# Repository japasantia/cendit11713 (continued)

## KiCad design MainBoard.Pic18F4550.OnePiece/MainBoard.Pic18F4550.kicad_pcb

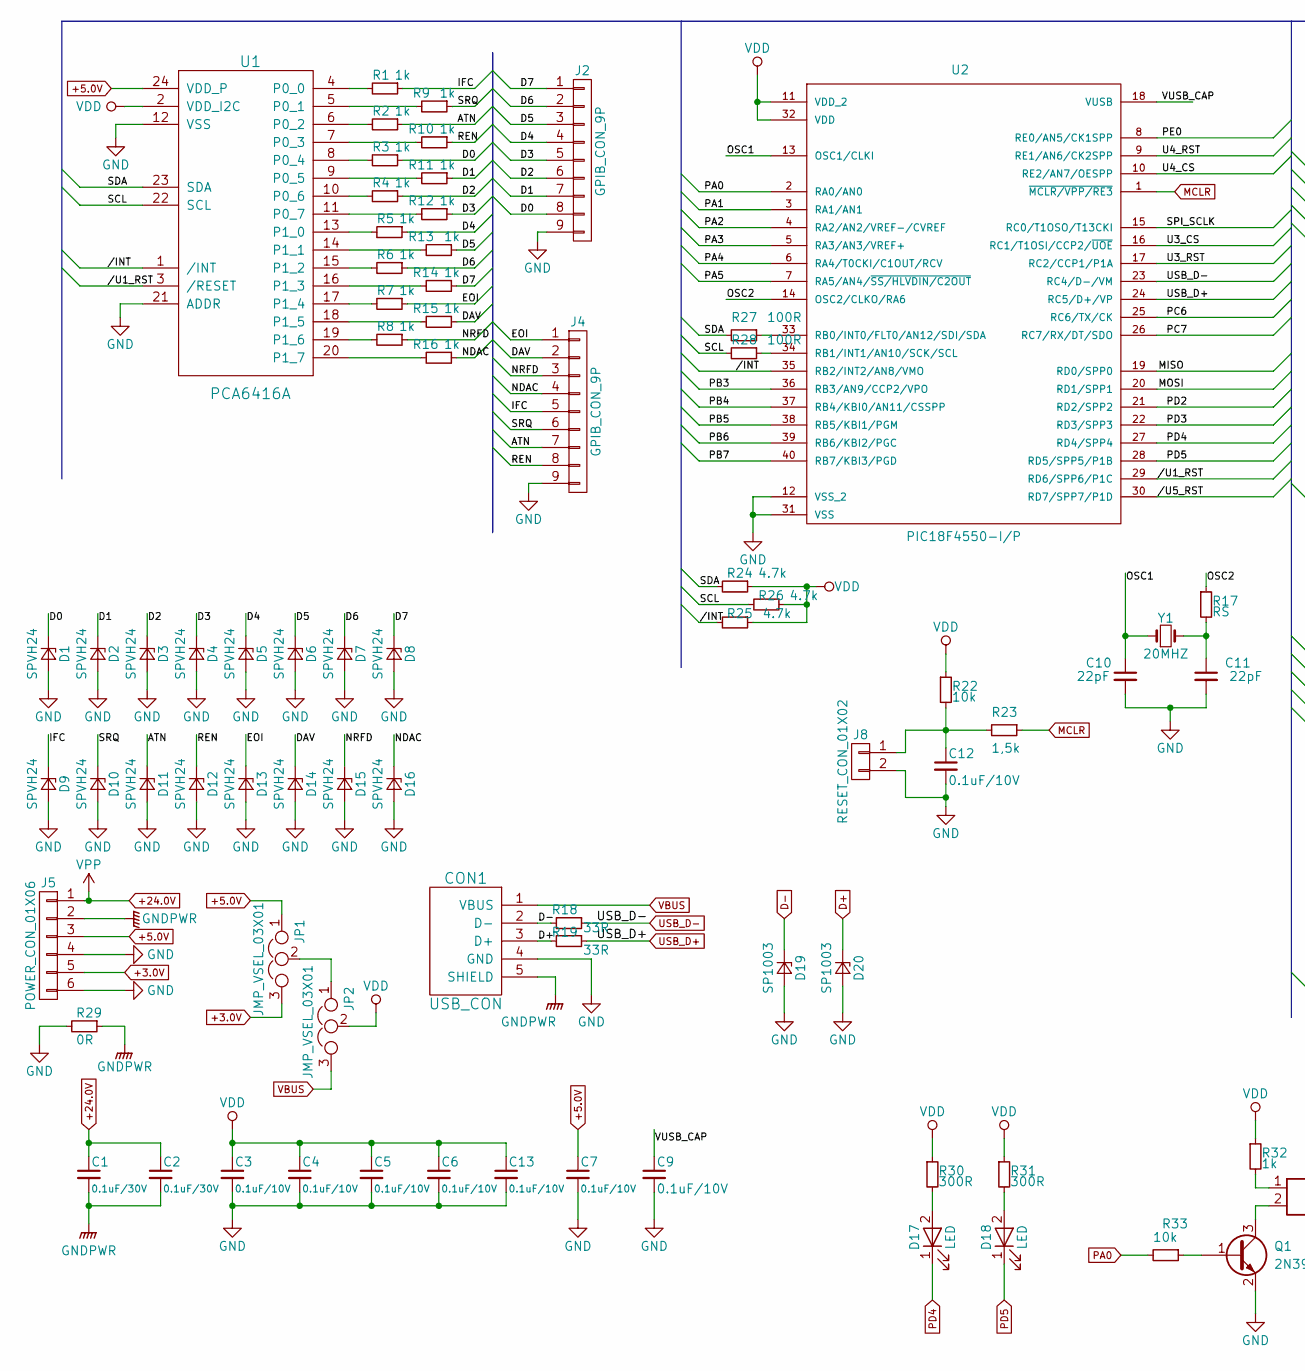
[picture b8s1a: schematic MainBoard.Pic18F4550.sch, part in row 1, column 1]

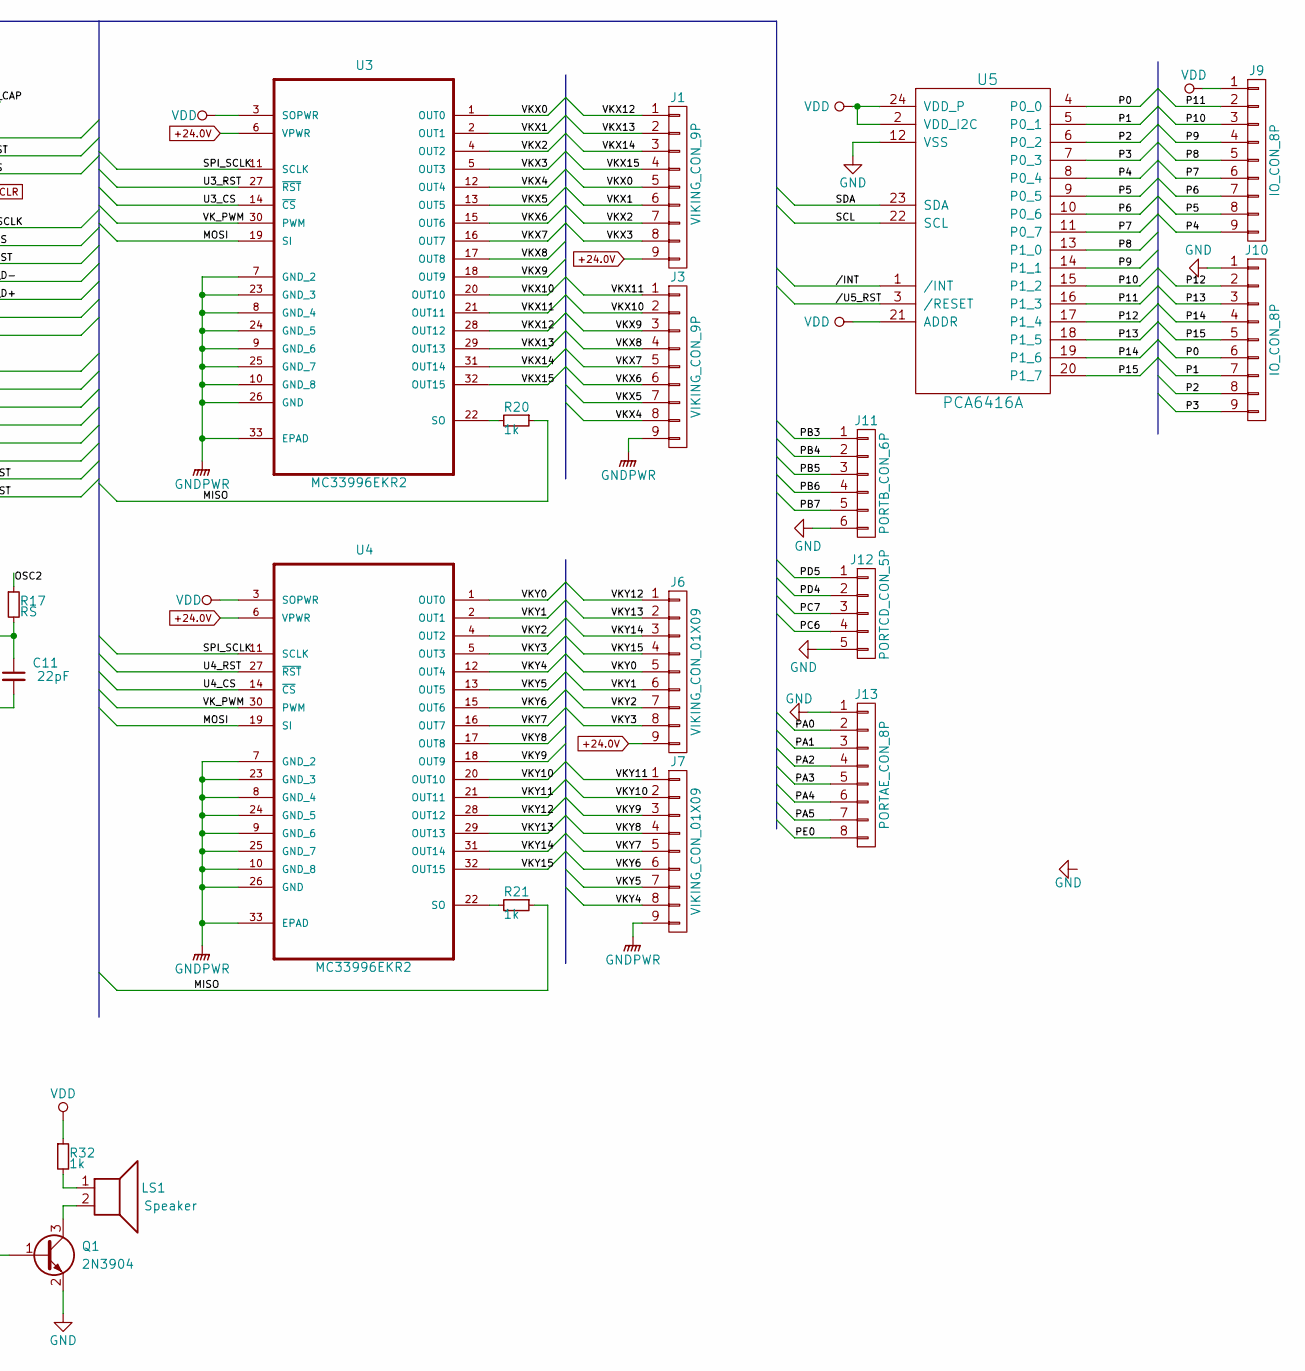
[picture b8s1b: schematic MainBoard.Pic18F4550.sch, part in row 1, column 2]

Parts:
C1, C2: 0.1uF/30V; C_1206_HandSoldering
C3, C4, C5, C6, C7, C13: 0.1uF/10V; C_1206_HandSoldering
C9, C12: 0.1uF/10V; C_0805_HandSoldering
C10, C11: 22pF; C_0805_HandSoldering
CON1: USB_CON; USB_SMT_B
D1, D2, D3, D4, D5, D6, D7, D8, D9, D10, D11, D12, D13, D14, D15, D16: SPVH24; SPHV24-SOD882
D17, D18: LED; LED_0805_HandSoldering
D19, D20: SP1003; SP1003-01ETG
J1, J3: VIKING_CON_9P; Pin_Header_Straight_1x09_Pitch2.54mm
J2, J4: GPIB_CON_9P; Pin_Header_Straight_1x09_Pitch2.54mm
J5: POWER_CON_01X06; Pin_Header_Straight_1x06_Pitch2.54mm
J6, J7: VIKING_CON_01X09; Pin_Header_Straight_1x09_Pitch2.54mm
J8: RESET_CON_01X02; Pin_Header_Straight_1x02_Pitch2.54mm
J9, J10: IO_CON_8P; Pin_Header_Straight_1x09_Pitch2.54mm
J11: PORTB_CON_6P; Pin_Header_Straight_1x06_Pitch2.54mm
J12: PORTCD_CON_5P; Pin_Header_Straight_1x05_Pitch2.54mm
J13: PORTAE_CON_8P; Pin_Header_Straight_1x08_Pitch2.54mm
JP1, JP2: JMP_VSEL_03X01; Pin_Header_Straight_1x03_Pitch2.54mm
LS1: Speaker; MagneticBuzzer_Kingstate_KCG0601
Q1: 2N3904; SOT-23
R1, R2, R3, R4, R5, R6, R7, R8, R9, R10, R11, R12, R13, R14, R15, R16, R20, R21, R32: 1k; R_0805_HandSoldering
R17: RS; R_0805_HandSoldering
R18, R19: 33R; R_0805_HandSoldering
R22, R33: 10k; R_0805_HandSoldering
R23: 1,5k; R_0805_HandSoldering
R24, R25, R26: 4.7k; R_0805_HandSoldering
R27, R28: 100R; R_0805_HandSoldering
R29: 0R; R_0805_HandSoldering
R30, R31: 300R; R_0805_HandSoldering
U1, U5: PCA6416A; PCA6416A-TSSOP24
U2: PIC18F4550-I/P; PIC18F4550-PDIP
U3, U4: MC33996EKR2; MC33996-SOIC32
Y1: 20MHZ; Crystal_SMD_HC49-SD

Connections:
+3.0V: J5.5, JP1.3
+5.0V: C7.1, J5.3, JP1.1, U1.24 (VDD_P)
+24.0V: C1.1, C2.1, J1.9, J5.1, J6.9, U3.6 (VPWR), U4.6 (VPWR)
//INT: R25.2, U1.1 (/INT), U2.35 (RB2/INT2/AN8/VMO), U5.1 (/INT)
//U1_RST: U1.3 (/RESET), U2.29 (RD6/SPP6/P1C)
//U5_RST: U2.30 (RD7/SPP7/P1D), U5.3 (/RESET)
/ATN: D11.1 (K), J4.7, R2.1
/D0: D1.1 (K), J2.8, R3.1
/D1: D2.1 (K), J2.7, R11.1
/D2: D3.1 (K), J2.6, R4.1
/D3: D4.1 (K), J2.5, R12.1
/D4: D5.1 (K), J2.4, R5.1
/D5: D6.1 (K), J2.3, R13.1
/D6: D7.1 (K), J2.2, R6.1
/D7: D8.1 (K), J2.1, R14.1
/DAV: D14.1 (K), J4.2, R15.1
/EOI: D13.1 (K), J4.1, R7.1
/IFC: D9.1 (K), J4.5, R1.1
/MISO: R20.1, R21.1, U2.19 (RD0/SPP0)
/MOSI: U2.20 (RD1/SPP1), U3.19 (SI), U4.19 (SI)
/NDAC: D16.1 (K), J4.4, R16.1
/NRFD: D15.1 (K), J4.3, R8.1
/OSC1: C10.1, U2.13 (OSC1/CLKI), Y1.1
/OSC2: R17.1, U2.14 (OSC2/CLKO/RA6)
/P0: J10.6, U5.4 (P0_0)
/P1: J10.7, U5.5 (P0_1)
/P2: J10.8, U5.6 (P0_2)
/P3: J10.9, U5.7 (P0_3)
/P4: J9.9, U5.8 (P0_4)
/P5: J9.8, U5.9 (P0_5)
/P6: J9.7, U5.10 (P0_6)
/P7: J9.6, U5.11 (P0_7)
/P8: J9.5, U5.13 (P1_0)
/P9: J9.4, U5.14 (P1_1)
/P10: J9.3, U5.15 (P1_2)
/P11: J9.2, U5.16 (P1_3)
/P12: J10.2, U5.17 (P1_4)
/P13: J10.3, U5.18 (P1_5)
/P14: J10.4, U5.19 (P1_6)
/P15: J10.5, U5.20 (P1_7)
/PA1: J13.3, U2.3 (RA1/AN1)
/PA2: J13.4, U2.4 (RA2/AN2/VREF-/CVREF)
/PA3: J13.5, U2.5 (RA3/AN3/VREF+)
/PA4: J13.6, U2.6 (RA4/T0CKI/C1OUT/RCV)
/PA5: J13.7, U2.7 (RA5/AN4/~SS/HLVDIN/C2OUT)
/PB3: J11.1, U2.36 (RB3/AN9/CCP2/VPO)
/PB4: J11.2, U2.37 (RB4/KBI0/AN11/CSSPP)
/PB5: J11.3, U2.38 (RB5/KBI1/PGM)
/PB6: J11.4, U2.39 (RB6/KBI2/PGC)
/PB7: J11.5, U2.40 (RB7/KBI3/PGD)
/PC6: J12.4, U2.25 (RC6/TX/CK)
/PC7: J12.3, U2.26 (RC7/RX/DT/SDO)
/PE0: J13.8, U2.8 (RE0/AN5/CK1SPP)
/REN: D12.1 (K), J4.8, R10.1
/SCL: R26.2, R28.2, U1.22 (SCL), U5.22 (SCL)
/SDA: R24.2, R27.2, U1.23 (SDA), U5.23 (SDA)
/SPI_SCLK: U2.15 (RC0/T1OSO/T13CKI), U3.11 (SCLK), U4.11 (SCLK)
/SRQ: D10.1 (K), J4.6, R9.1
/U3_CS: U2.16 (RC1/T1OSI/CCP2/~UOE), U3.14 (~CS)
/U3_RST: U2.17 (RC2/CCP1/P1A), U3.27 (~RST)
/U4_CS: U2.10 (RE2/AN7/OESPP), U4.14 (~CS)
/U4_RST: U2.9 (RE1/AN6/CK2SPP), U4.27 (~RST)
/VKX0: J1.5, U3.1 (OUT0)
/VKX1: J1.6, U3.2 (OUT1)
/VKX2: J1.7, U3.4 (OUT2)
/VKX3: J1.8, U3.5 (OUT3)
/VKX4: J3.8, U3.12 (OUT4)
/VKX5: J3.7, U3.13 (OUT5)
/VKX6: J3.6, U3.15 (OUT6)
/VKX7: J3.5, U3.16 (OUT7)
/VKX8: J3.4, U3.17 (OUT8)
/VKX9: J3.3, U3.18 (OUT9)
/VKX10: J3.2, U3.20 (OUT10)
/VKX11: J3.1, U3.21 (OUT11)
/VKX12: J1.1, U3.28 (OUT12)
/VKX13: J1.2, U3.29 (OUT13)
/VKX14: J1.3, U3.31 (OUT14)
/VKX15: J1.4, U3.32 (OUT15)
/VKY0: J6.5, U4.1 (OUT0)
/VKY1: J6.6, U4.2 (OUT1)
/VKY2: J6.7, U4.4 (OUT2)
/VKY3: J6.8, U4.5 (OUT3)
/VKY4: J7.8, U4.12 (OUT4)
/VKY5: J7.7, U4.13 (OUT5)
/VKY6: J7.6, U4.15 (OUT6)
/VKY7: J7.5, U4.16 (OUT7)
/VKY8: J7.4, U4.17 (OUT8)
/VKY9: J7.3, U4.18 (OUT9)
/VKY10: J7.2, U4.20 (OUT10)
/VKY11: J7.1, U4.21 (OUT11)
/VKY12: J6.1, U4.28 (OUT12)
/VKY13: J6.2, U4.29 (OUT13)
/VKY14: J6.3, U4.31 (OUT14)
/VKY15: J6.4, U4.32 (OUT15)
/VK_PWM: U3.30 (PWM), U4.30 (PWM)
/VUSB_CAP: C9.1, U2.18 (VUSB)
D+: CON1.3 (D+), D20.1 (K), R19.2
D-: CON1.2 (D-), D19.1 (K), R18.2
GND: C3.2, C4.2, C5.2, C6.2, C7.2, C9.2, C10.2, C11.2, C12.2, C13.2, CON1.4 (GND), D1.2 (A), D2.2 (A), D3.2 (A), D4.2 (A), D5.2 (A), D6.2 (A), D7.2 (A), D8.2 (A), D9.2 (A), D10.2 (A), D11.2 (A), D12.2 (A), D13.2 (A), D14.2 (A), D15.2 (A), D16.2 (A), D19.2 (A), D20.2 (A), J2.9, J4.9, J5.4, J5.6, J8.2, J10.1, J11.6, J12.5, J13.1, Q1.2 (E), R29.2, U1.12 (VSS), U1.21 (ADDR), U2.12 (VSS_2), U2.31 (VSS), U5.12 (VSS)
GNDPWR: C1.2, C2.2, CON1.5 (SHIELD), J3.9, J5.2, J7.9, R29.1, U3.7 (GND_2), U3.8 (GND_4), U3.9 (GND_6), U3.10 (GND_8), U3.23 (GND_3), U3.24 (GND_5), U3.25 (GND_7), U3.26 (GND), U3.33 (EPAD), U4.7 (GND_2), U4.8 (GND_4), U4.9 (GND_6), U4.10 (GND_8), U4.23 (GND_3), U4.24 (GND_5), U4.25 (GND_7), U4.26 (GND), U4.33 (EPAD)
MCLR: R23.1, U2.1 (~MCLR/VPP/RE3)
unnamed: C11.1, R17.2, Y1.2
unnamed: C12.1, J8.1, R22.2, R23.2
unnamed: D17.2 (A), R30.2
unnamed: D18.2 (A), R31.2
unnamed: JP1.2, JP2.1
unnamed: LS1.1, R32.2
unnamed: LS1.2, Q1.3 (C)
unnamed: Q1.1 (B), R33.1
unnamed: R1.2, U1.4 (P0_0)
unnamed: R2.2, U1.6 (P0_2)
unnamed: R3.2, U1.8 (P0_4)
unnamed: R4.2, U1.10 (P0_6)
unnamed: R5.2, U1.13 (P1_0)
unnamed: R6.2, U1.15 (P1_2)
unnamed: R7.2, U1.17 (P1_4)
unnamed: R8.2, U1.19 (P1_6)
unnamed: R9.2, U1.5 (P0_1)
unnamed: R10.2, U1.7 (P0_3)
unnamed: R11.2, U1.9 (P0_5)
unnamed: R12.2, U1.11 (P0_7)
unnamed: R13.2, U1.14 (P1_1)
unnamed: R14.2, U1.16 (P1_3)
unnamed: R15.2, U1.18 (P1_5)
unnamed: R16.2, U1.20 (P1_7)
unnamed: R20.2, U3.22 (SO)
unnamed: R21.2, U4.22 (SO)
unnamed: R27.1, U2.33 (RB0/INT0/FLT0/AN12/SDI/SDA)
unnamed: R28.1, U2.34 (RB1/INT1/AN10/SCK/SCL)
PA0: J13.2, R33.2, U2.2 (RA0/AN0)
PD4: D17.1 (K), J12.2, U2.27 (RD4/SPP4)
PD5: D18.1 (K), J12.1, U2.28 (RD5/SPP5/P1B)
USB_D+: R19.1, U2.24 (RC5/D+/VP)
USB_D-: R18.1, U2.23 (RC4/D-/VM)
VBUS: CON1.1 (VBUS), JP2.3
VDD: C3.1, C4.1, C5.1, C6.1, C13.1, J9.1, JP2.2, R22.1, R24.1, R25.1, R26.1, R30.1, R31.1, R32.1, U1.2 (VDD_I2C), U2.11 (VDD_2), U2.32 (VDD), U3.3 (SOPWR), U4.3 (SOPWR), U5.2 (VDD_I2C), U5.21 (ADDR), U5.24 (VDD_P)

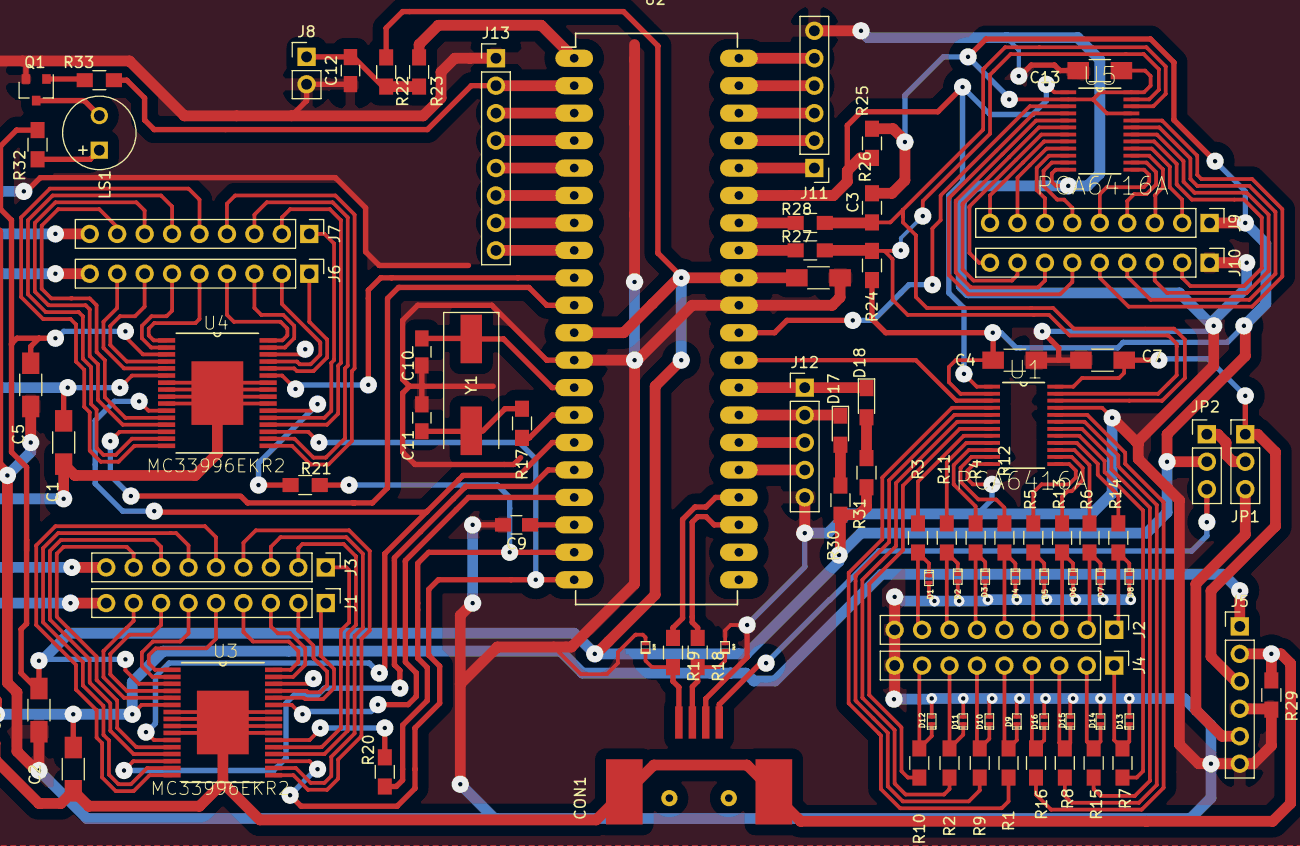
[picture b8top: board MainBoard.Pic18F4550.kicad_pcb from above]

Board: 2 copper layers, 89 parts (0 on the bottom side), 136 nets.

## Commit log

2018-01-09 Commit para restaurar repo
    - Respaldo ante problemas en pull
2018-01-13 Revision de PCBs + MergedPcbs
    - Se revisan PCBs
    - VikingPortExpander
    - GpibPortExpander
    - MainBoards en tres versiones
    - Se genera archivos Gerber que combina estos PCBs en un documento
2018-01-15 Revision de MainBoard.OnePiece
2018-01-16 Revision de merged PCBs
    - Ultima revision para fabricacion PCBs
    - No se hacen cambios en este con respecto al commit anterior
2018-01-18 Respaldo de archivos modificados
    - Aparecend modificados, pero no se ha trabajado en ellos
2018-01-29 Se comienza diseño de interfaz fìsica: teclado + pantalla
    - Tarjeta PCB que contiene teclado matricial + pantalla LCD
    - Trabaja con el expansor de puertos PCA6416A
2018-02-01 Revision de PCbs + generacion de nuevos archivos Gerber
    - Se corrigen pads de pin headers
    - Se revisan
    - MainBoard option 2
    - PortExpander MC33996.Option3
    - GpibPortExpanderPCA6408A.Option3
    - Se generan Gerber + Vistas 3D
2018-02-05 Revision de PCBs + generacion nuevos gerber
    - Se hacen ligeras correcciones en los PCBs (5)
    - Se genera nuevamente archivo PCBs combinados
    - Se generan nuevos archivos gerber
2018-02-05 Se genera documentos diseño MergedPcbs
    - Se combinan nuevamente 6 PCBs en un documento
    - Se generan archivos gerber
    - Se envian para manufactura
